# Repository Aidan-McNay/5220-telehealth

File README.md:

# 5220-telehealth

A repository of our design for MAE 5220: Introduction to IoT, which
obtains blood pressure data from an Omron Evolv BP7000, and transmits
it over LoRaWAN to The Things Network (TTN).

Unlike the code for the rest of the class, our target platform is a
Raspberry Pi Pico W, so the build process is different than labs.

## Repository Structure

 - **CMakeLists.txt**: Instructions for our CMake-based build system
 - **app**: Target applications for the Pico W (each with a `main`)
 - **ble**: Source code for interfacing over BLE
 - **cmake**: Extra CMake utilities
 - **lorawan**: Source code for interfacing over LoRaWAN
 - **lorawan-library-for-pico**: A submodule library for using LoRaWAN on the Pico W
 - **pcb**: Our PCB design for the system
 - **pico_sdk_import.cmake**: CMake support for the Raspberry Pi SDK
 - **ui**: Source code for interfacing with physical UI devices (LEDs, buttons, etc.)
 - **utils**: Utility code used throughout the project

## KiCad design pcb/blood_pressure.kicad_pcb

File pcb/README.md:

# pcb

PCB design. The files marked with "original" show the PCB that we ordered with the PMOS footprint mismatch as described in our report.

The current layout and schematic contain the updated PCB with the mismatch fixed. To produce the current PCB, use corrected_gerberdrill.zip when ordering from JLBPCB.

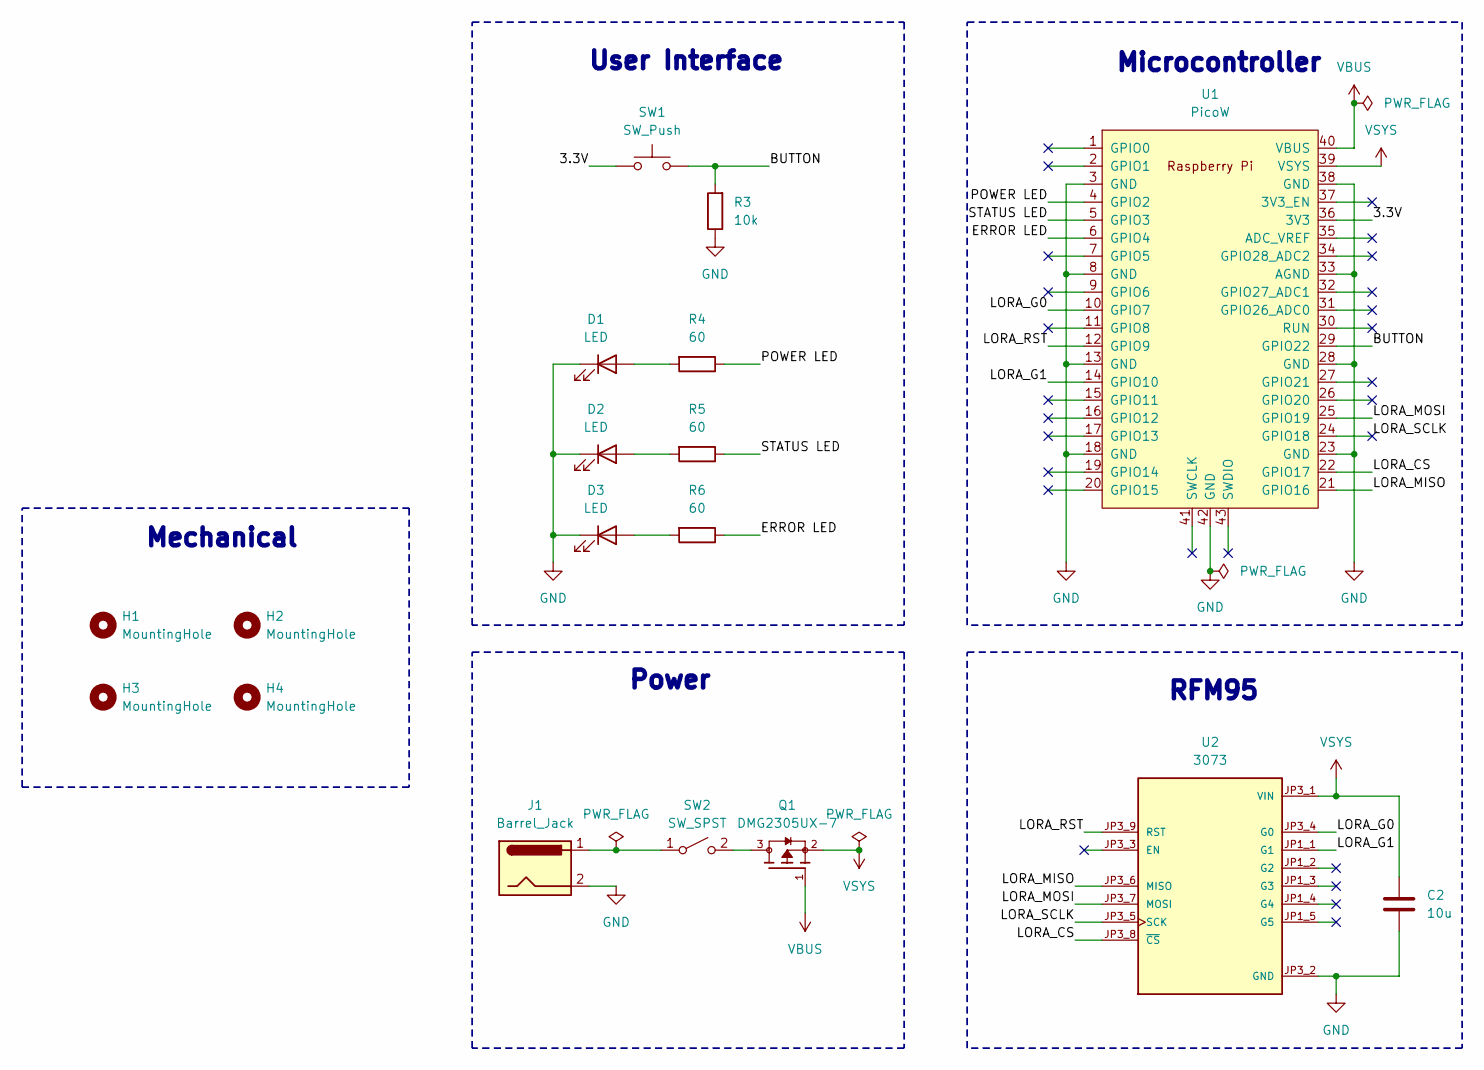
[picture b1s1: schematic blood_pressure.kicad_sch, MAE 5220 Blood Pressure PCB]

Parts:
C2: 10u; C_0805_2012Metric
D1, D2, D3: LED; LED_D5.0mm_Clear
H1, H2, H3, H4: MountingHole; MountingHole_3.2mm_M3
J1: Barrel_Jack; BarrelJack_CUI_PJ-102AH_Horizontal
Q1: DMG2305UX-7; SOT91P240X110-3N_DMG2305UX-7; PARTREV 09/2018
R3: 10k; R_0805_2012Metric
R4, R5, R6: 60; R_0805_2012Metric
SW1: SW_Push; SW_PUSH_6mm
SW2: SW_SPST; SW_DIP_SPSTx01_Slide_6.7x4.1mm_W7.62mm_P2.54mm_LowProfile
U1: PicoW; RPi_PicoW_SMD_TH
U2: 3073; rfm; PARTREV 2023-10-24

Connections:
/3.3V: SW1.1, U1.36 (3V3)
/BUTTON: R3.2, SW1.2, U1.29 (GPIO22)
/ERROR LED: R6.1, U1.6 (GPIO4)
/LORA_CS: U1.22 (GPIO17), U2.JP3_8 (~CS)
/LORA_G0: U1.10 (GPIO7), U2.JP3_4 (G0)
/LORA_G1: U1.14 (GPIO10), U2.JP1_1 (G1)
/LORA_MISO: U1.21 (GPIO16), U2.JP3_6 (MISO)
/LORA_MOSI: U1.25 (GPIO19), U2.JP3_7 (MOSI)
/LORA_RST: U1.12 (GPIO9), U2.JP3_9 (RST)
/LORA_SCLK: U1.24 (GPIO18), U2.JP3_5 (SCK)
/POWER LED: R4.1, U1.4 (GPIO2)
/STATUS LED: R5.1, U1.5 (GPIO3)
GND: C2.2, D1.1 (K), D2.1 (K), D3.1 (K), J1.2, R3.1, U1.3 (GND), U1.8 (GND), U1.13 (GND), U1.18 (GND), U1.23 (GND), U1.28 (GND), U1.33 (AGND), U1.38 (GND), U1.42 (GND), U2.JP3_2 (GND)
unnamed: D1.2 (A), R4.2
unnamed: D2.2 (A), R5.2
unnamed: D3.2 (A), R6.2
unnamed: J1.1, SW2.1 (A)
unnamed: Q1.3, SW2.2 (B)
VBUS: Q1.1, U1.40 (VBUS)
VSYS: C2.1, Q1.2, U1.39 (VSYS), U2.JP3_1 (VIN)

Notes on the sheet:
Microcontroller
RFM95
User Interface
Mechanical
Power

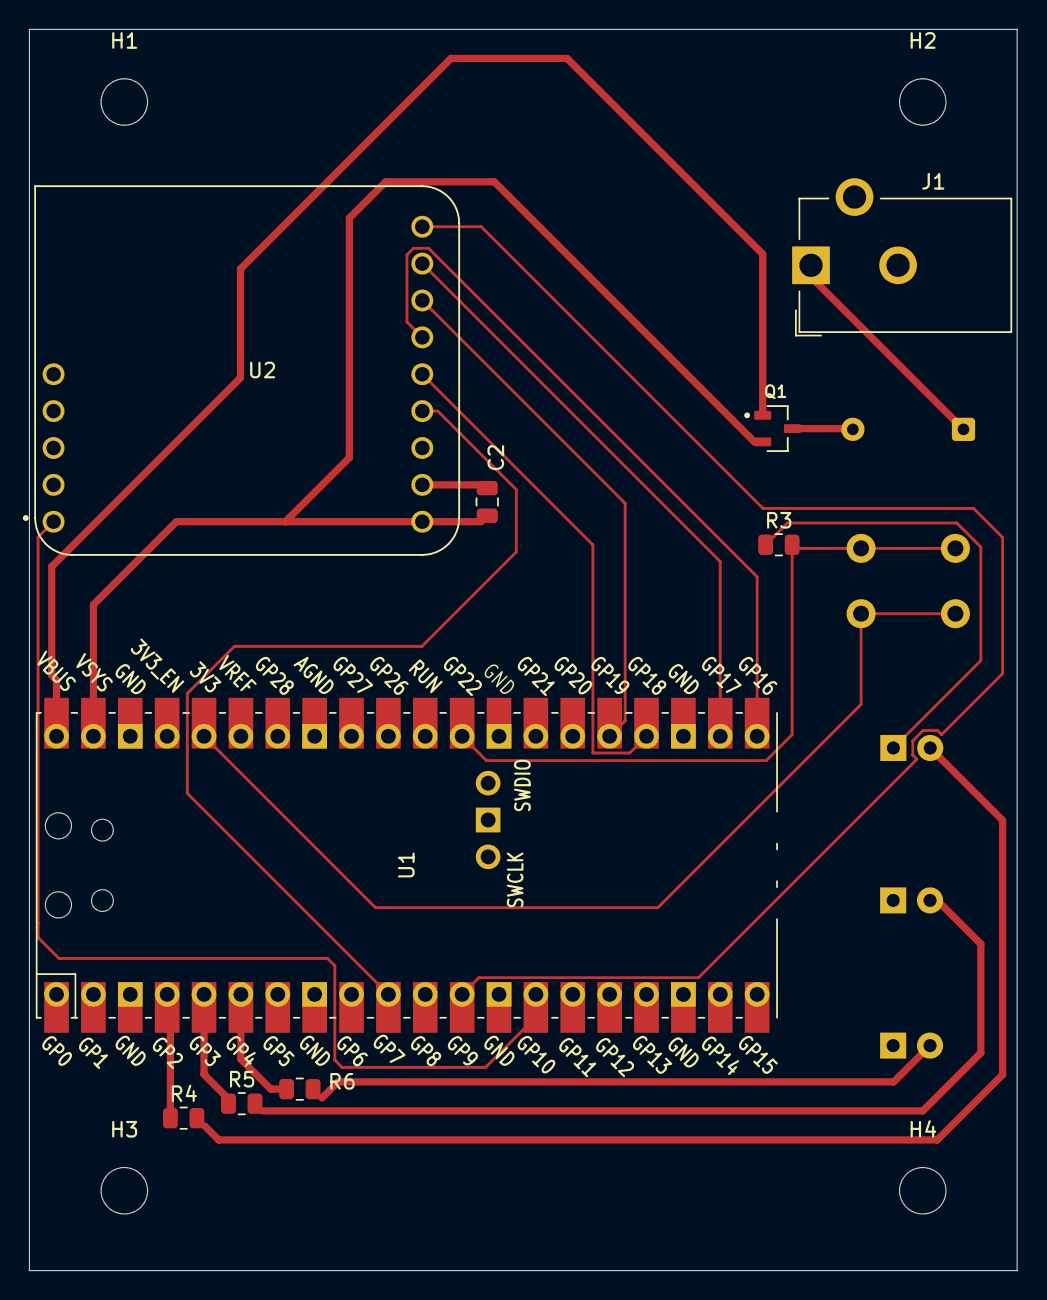
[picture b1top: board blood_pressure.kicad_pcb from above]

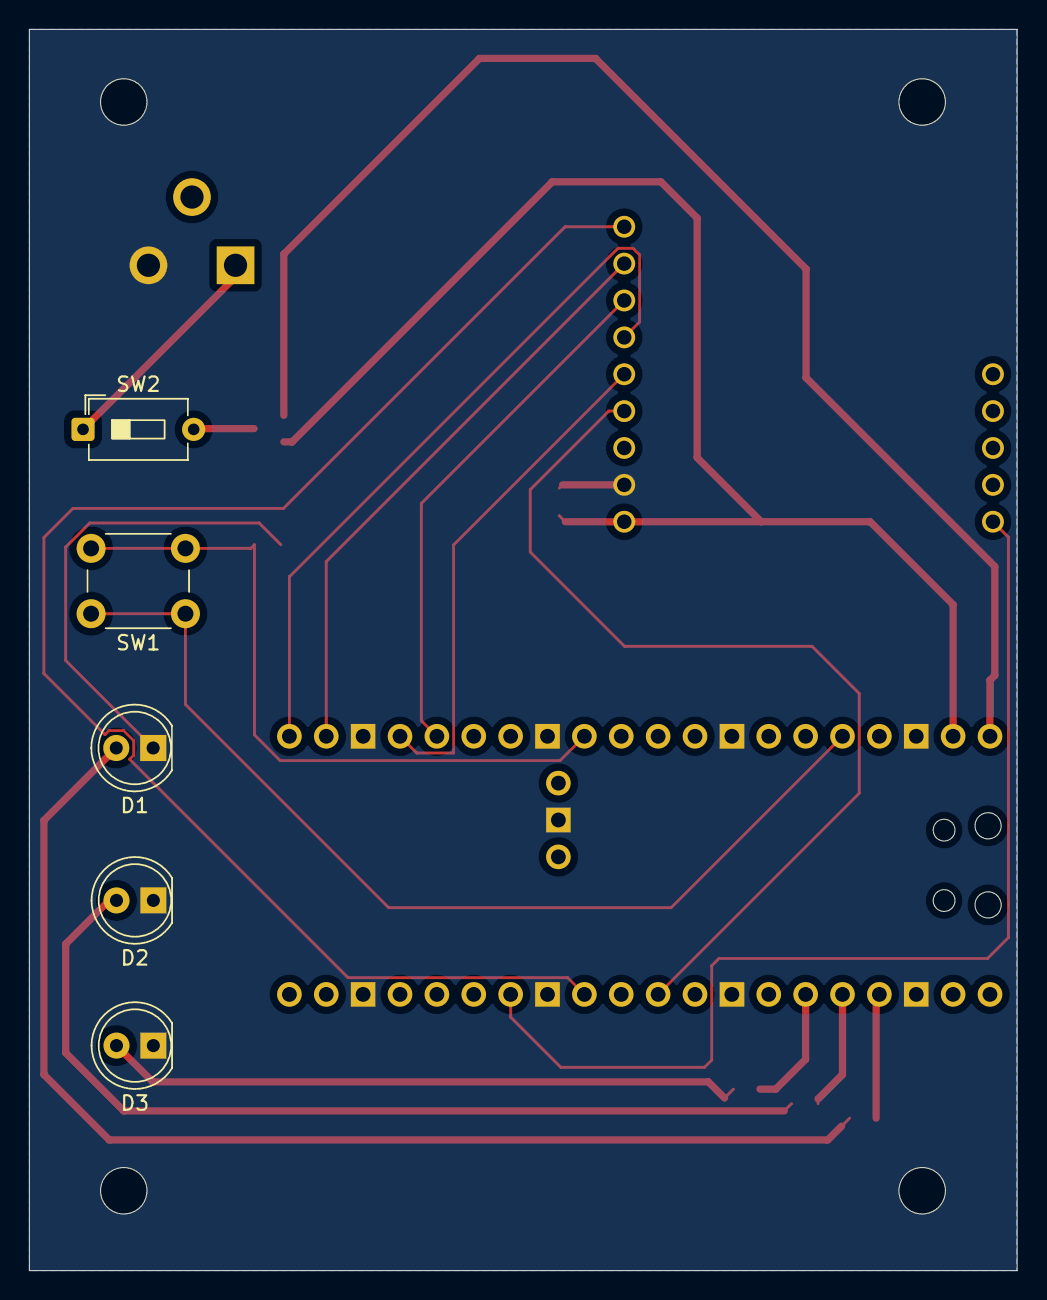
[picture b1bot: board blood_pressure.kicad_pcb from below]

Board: 4 copper layers, 68.0 x 85.5 mm, 18 parts (5 on the bottom side), 20 nets.

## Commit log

2025-03-05 Initial .gitignore
2025-04-07 Initial compiler setup
2025-04-07 Added subdirectories for code organization
2025-04-09 Initial PCB
2025-04-09 Working on BLE, button boilerplate
2025-04-11 starting to connect to TTN
2025-04-11 Working on BLE client
2025-04-12 BLE client compiles, not tested
2025-04-12 Restructure build, demo untested
2025-04-12 Remove dead code
2025-04-12 Work in progress, but can connect!
2025-04-12 Print UUID128 (still need to enable multiple services
2025-04-12 Multiple service discovery
2025-04-16 Final schematic
2025-04-17 Final PCB
2025-04-18 Schematic
2025-04-20 Support for indications
2025-04-20 Progress
2025-04-21 Working in progress (debugging notifications)
2025-04-21 Remove test line
2025-04-21 Added lorawan submodule
2025-04-21 Include cmake updates
2025-04-23 Fix library issues
2025-04-25 Add template LoRaWAN code
2025-04-27 Working on BLE
2025-04-27 Progress on notifications
2025-04-27 PAIRING WORKS
2025-04-27 Blood pressure successfully off device
2025-04-27 Fix printing
2025-04-27 Make README
2025-04-27 Add arterial pressure
2025-04-28 Final
2025-04-28 User interface added
2025-04-30 encryption folder
2025-05-02 state machine some progress
2025-05-02 LoRaWAN utilities
2025-05-02 LoRaWAN WIP
2025-05-02 fsm working
2025-05-09 Encryption code
2025-05-10 state machine stuff
2025-05-10 Python code
2025-05-10 Debugging...
2025-05-10 Working top-level
2025-05-11 Whoops forgot LoRaWAN library edits
2025-05-11 encryption beginning
2025-05-11 notebook edit
2025-05-11 Encryption code semi-final?
2025-05-11 quotes
2025-05-11 Key correction
2025-05-11 some encryption debugging
2025-05-11 yippee yippee yippee
2025-05-11 Python notebook edit
2025-05-11 state machine fixing interface
2025-05-11 Python script
2025-05-11 error stuff looped
2025-05-11 Revert, factor out key
2025-05-11 erased debug statements
2025-05-11 unencrypted working w 6 bytes
2025-05-11 Include encryption in state machine
2025-05-11 process2.py and process3.py
    process2 dumps raw unparsed data into txt file and works. process3 is going to parsed into csv file
2025-05-11 process3.py works
2025-05-15 Read Me Files
